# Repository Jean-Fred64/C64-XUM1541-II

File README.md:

# C64 XUM1541-II

# 1> Documentation
When you're ready to start installing software, by first installing the firmware onto the *Arduino Pro Micro* and then installing OpenCBM, there's a separate document covering these details:
- [Firmware installation](https://github.com/Jean-Fred64/C64-XUM1541-II/blob/Jean-Fred/documentation/firmware.md)

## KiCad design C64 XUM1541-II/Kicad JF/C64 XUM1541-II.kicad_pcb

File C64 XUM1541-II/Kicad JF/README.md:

Version Kicad with DIN 10 mm and 5 mm

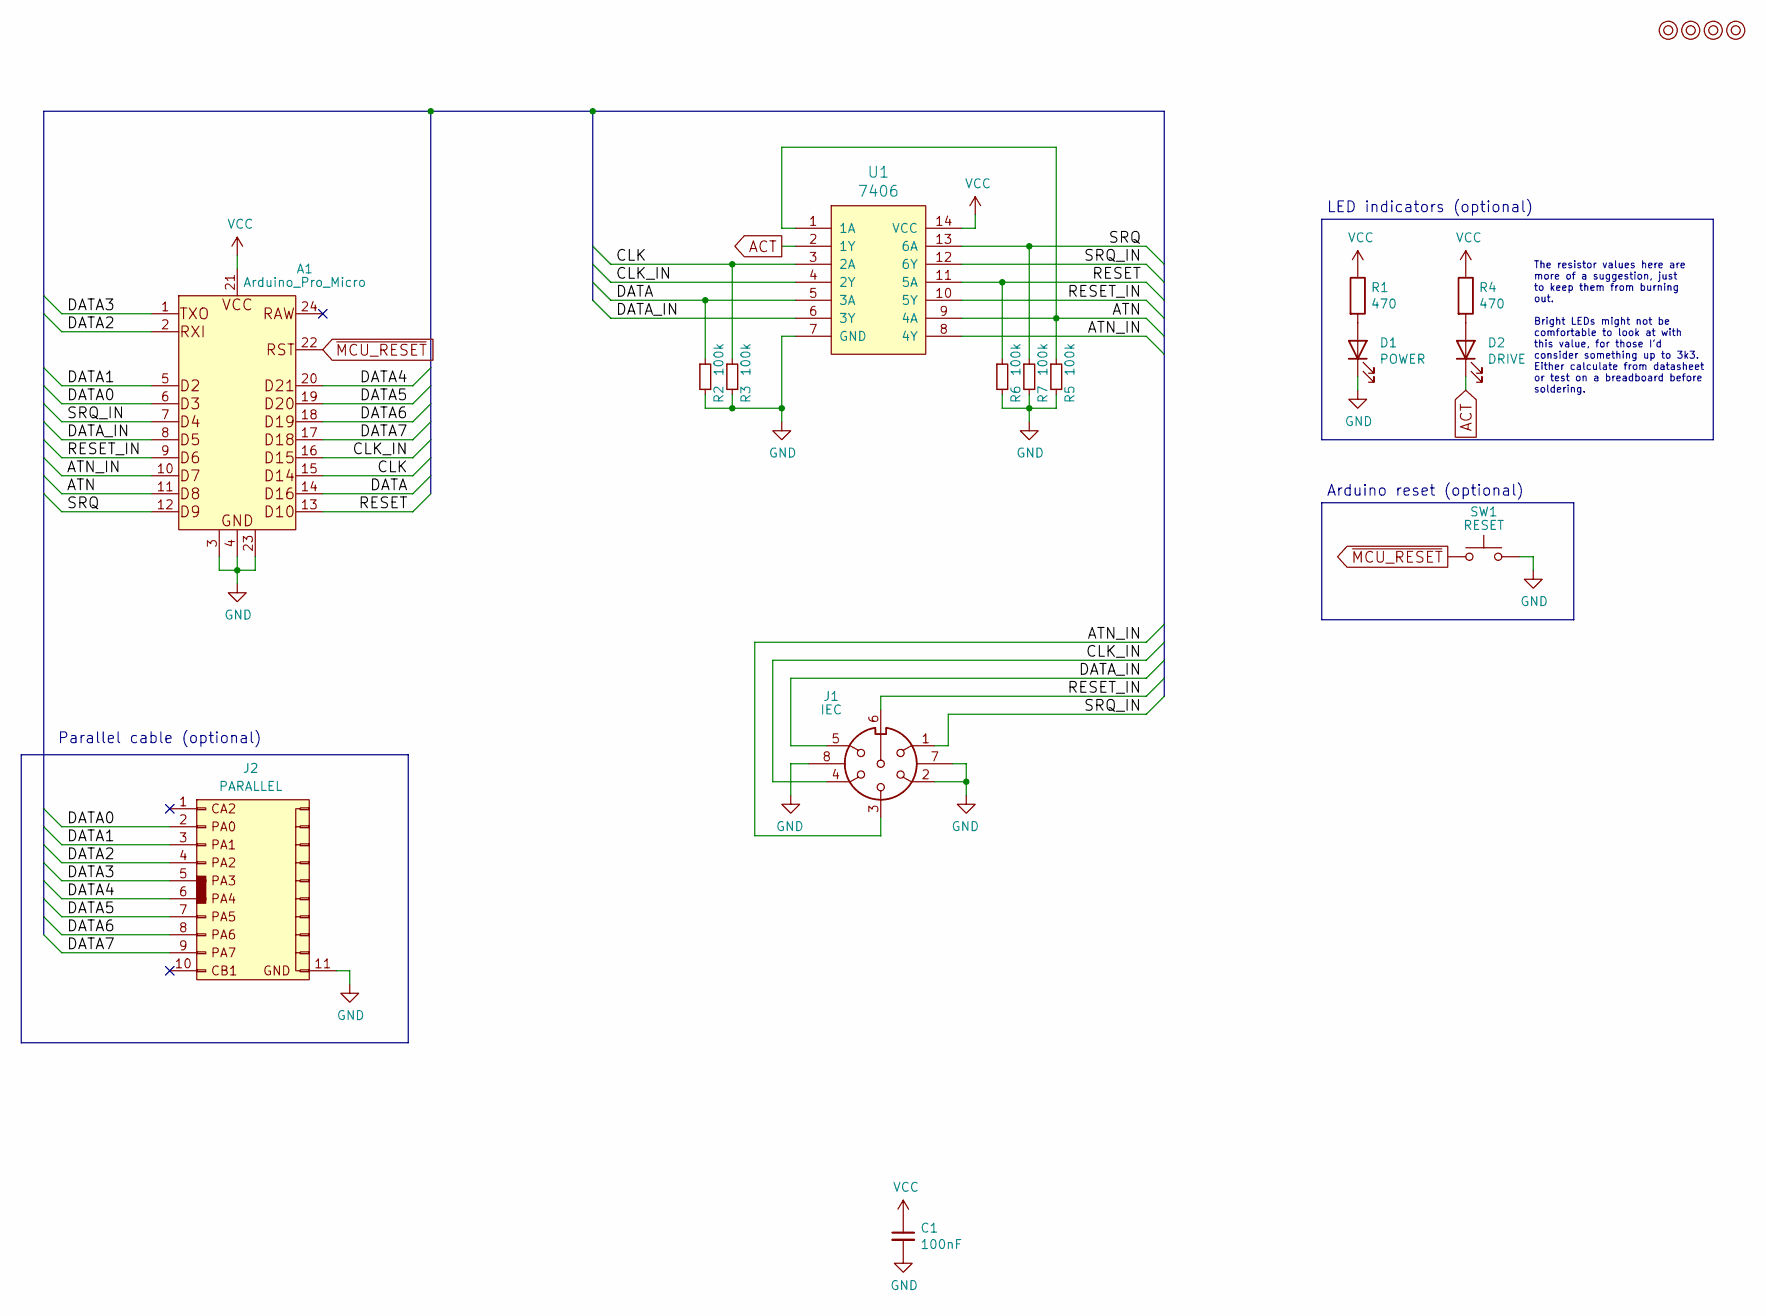
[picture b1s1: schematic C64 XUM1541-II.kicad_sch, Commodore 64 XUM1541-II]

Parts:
A1: Arduino_Pro_Micro
C1: 100nF; C_Disc_D4.7mm_W2.5mm_P5.00mm
D1: POWER; LED_D5.0mm
D2: DRIVE; LED_D5.0mm
J1: IEC; C64_IEC
J2: PARALLEL; SpeedDOS_IDC
M1, M2, M3, M4: Mounting; M3_pin
R1, R4: 470; R_Axial_DIN0207_L6.3mm_D2.5mm_P10.16mm_Horizontal
R2, R3, R5, R6, R7: 100k; R_Axial_DIN0207_L6.3mm_D2.5mm_P10.16mm_Horizontal
SW1: RESET; SW_PUSH_6mm
U1: 7406; DIP-14_W7.62mm_Socket_LongPads

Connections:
/ATN: A1.11 (D8), R5.1, U1.1 (1A), U1.9 (4A)
/ATN_IN: A1.10 (D7), J1.3, U1.8 (4Y)
/CLK: A1.15 (D14), R3.1, U1.3 (2A)
/CLK_IN: A1.16 (D15), J1.4, U1.4 (2Y)
/DATA: A1.14 (D16), R2.1, U1.5 (3A)
/DATA0: A1.6 (D3), J2.2
/DATA1: A1.5 (D2), J2.3
/DATA2: A1.2 (RXI), J2.4
/DATA3: A1.1 (TXO), J2.5
/DATA4: A1.20 (D21), J2.6
/DATA5: A1.19 (D20), J2.7 (Pin_5)
/DATA6: A1.18 (D19), J2.8
/DATA7: A1.17 (D18), J2.9
/DATA_IN: A1.8 (D5), J1.5, U1.6 (3Y)
/RESET: A1.13 (D10), R6.1, U1.11 (5A)
/RESET_IN: A1.9 (D6), J1.6, U1.10 (5Y)
/SRQ: A1.12 (D9), R7.1, U1.13 (6A)
/SRQ_IN: A1.7 (D4), J1.1, U1.12 (6Y)
ACT: D2.1 (K), U1.2 (1Y)
GND: A1.3 (GND), A1.4 (GND), A1.23 (GND), C1.2, D1.1 (K), J1.2, J1.7, J1.8, J2.11, R2.2, R3.2, R5.2, R6.2, R7.2, SW1.2, U1.7 (GND)
unnamed: D1.2 (A), R1.2
unnamed: D2.2 (A), R4.2
VCC: A1.21 (VCC), C1.1, R1.1, R4.1, U1.14 (VCC)
~MCU_RESET: A1.22 (RST), SW1.1

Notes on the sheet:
Parallel cable (optional)
Arduino reset (optional)
LED indicators (optional)
The resistor values here are more of a suggestion, just to keep them from burning out. Bright LEDs might not be comfortable to look at with this value, for those I'd consider something up to 3k3. Either calculate from datasheet or test on a breadboard before soldering.

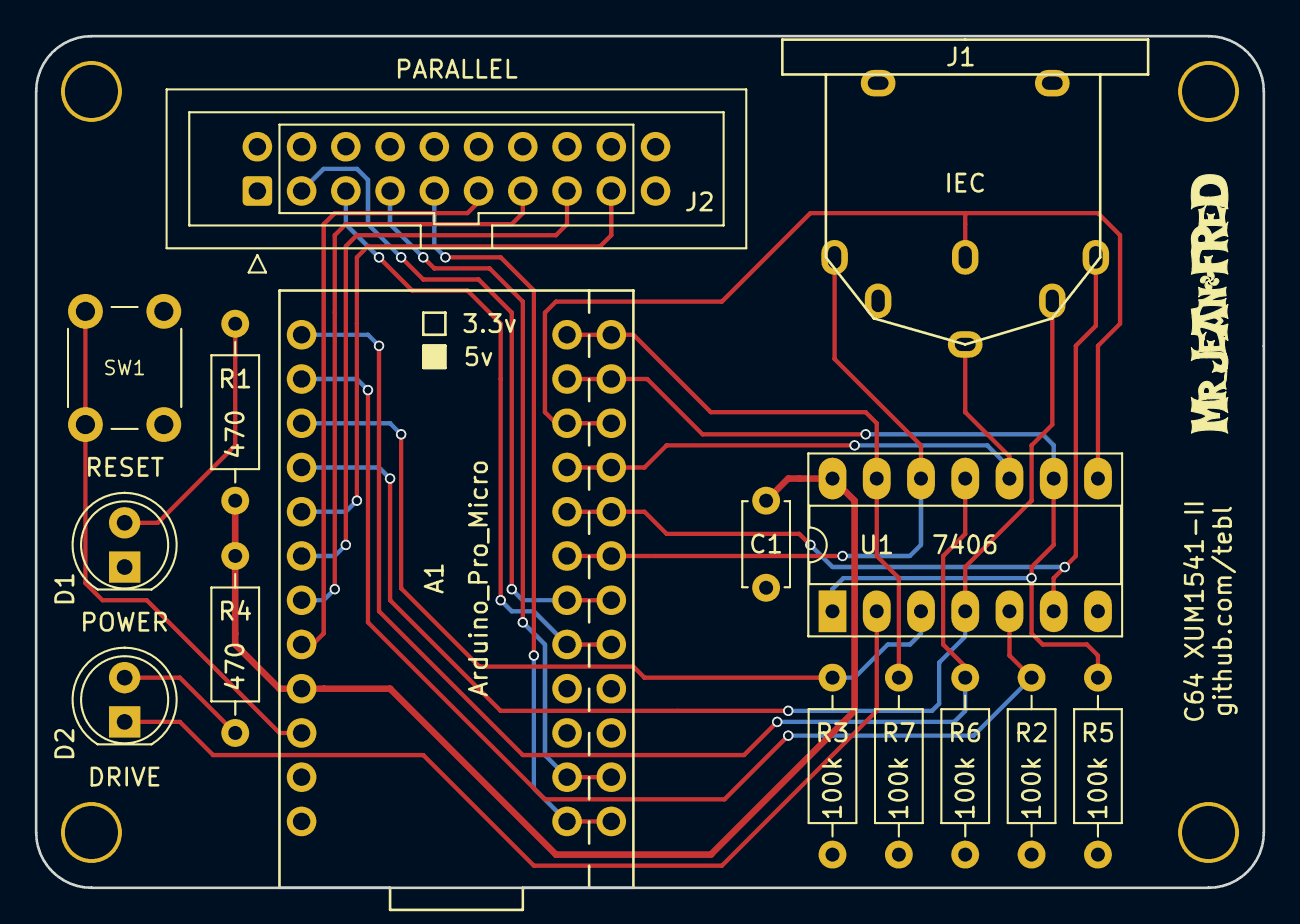
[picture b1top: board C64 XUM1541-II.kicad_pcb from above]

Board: 2 copper layers, 70.5 x 48.9 mm, 19 parts (0 on the bottom side), 24 nets.

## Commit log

2022-11-28 Create export JF 10mm
2022-11-28 Rename version DIN 5mm & 10 mm.md to README.md

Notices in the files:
C64 XUM1541-II/Kicad JF/C64 XUM1541-II.kicad_pcb:
Licensed under
CERN OHL v.1.2
